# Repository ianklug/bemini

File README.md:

# Bemini
A miniature mechanical keyboard controller with a rotary encoder for staggered-key rhythm games.

Design by [ianklug](https://ianklug.com). Art by [clue](https://clue.graphics).

Special thanks to [Sebastiaan Swinkels](https://github.com/C44Supra) for technical assistance.

Made with [KiCad](https://www.kicad.org/) and [Blender](https://www.blender.org/).

*Please clone this repository using the `--recurse-submodules` flag. Some of the required symbol and footprint libraries will not be included otherwise.*

## Versions

*Please note that the RP2040 models are functional at a hardware level, but software is incomplete.*

The 2.x versions (bemini-rp) use the RP2040 MCU, and require different firmware from the 1.x versions. They also include a few new features and refinements over the 1.x models, including M2 mounting holes and an RGB indicator LED.

The 1.x versions (bemini-atmel) use the Atmega32U4 MCU, in either the MU or AU footprint. These versions are no longer recommended.

## Firmware

Bemini is powered by [QMK Firmware](https://qmk.fm).

Bemini ships with a customized keymap that is ideal for use with many common rhythm games. More information about the default keymap is available [here](https://kayboards.com/pages/bemini-keymap).

You may customize Bemini's keymap by following the instructions in [these documents](https://docs.qmk.fm). This will require a reflash of your board's firmware. Use [QMK Toolbox](https://github.com/qmk/qmk_toolbox) to flash if on Windows or MacOS, or the QMK CLI with avrdude on Linux.

## Printed Parts

The .stl files for Bemini's 3D-printed parts are included in the models directory. I print these parts on a [Prusa i3 MK3S](https://www.prusa3d.com/category/original-prusa-i3-mk3s/) in black PLA on a smooth steel print bed.

The newer turntable (v2) is a single piece, and requires no supports. It should be printed with the top facing down. Infill should be at least 15%. This is the recommended version.

The first turntable (v1) prints in two pieces (main and cap) which snap together. This may improve the quality of some of the touch surfaces if your prints are inconsistent. Print with the flat top of the cap facing down, and the flat ring (the bottom) of the main body facing down. The body will require supports.

The encoder retainer should be printed with the flat part facing down. Slide this piece in between the encoder's legs on the underside of the board to secure the encoder, if you do not wish to solder it in place.

## Manufacturing

**Manufacture at your own risk. I can not guarantee the quality or functionality of boards which are not sold directly by me.**

**Please note that most PCB manufacturers have a minimum order quantity of five units.**

Hand-soldering Beminis from scratch is extremely difficult and NOT recommended due to the small size of the surface-mount components and their pads. Instead, PCB assembly services can source and assemble all the small parts on the bottom of the board. Depending on the manufacturer, you may only need to hand-solder some of the larger parts, such as the USB port and the switch sockets.

I can personally recommend [JLCPCB](https://jlcpcb.com) or [PCBWay](https://pcbway.com/), but most PCB manufacturers should be capable of producing Bemini.

Zipped gerber files are present for the production designs of each variation of Bemini. They are called `<variation>-gerbers-<version>.zip` and should be compatible with most PCB manufacturing services.

If you will be ordering from JLCPCB, use `<variation>-gerbers-jlcpcb-<version>.zip`. These gerbers have the JLCPCB serial number placed in an easily-readable location on the back of the board. Make sure to choose "Specify a location" under "Remove Order Number" so that this number is printed where expected.

Production Beminis are two-layer FR4, 1.6mm thick. The RP2040 versions measure 220x70mm. They are assembled using lead-free solder. BOM and Centroid files are present for each board in the format expected by JLCPCB.

The USB connector is a [GCT USB4085](https://gct.co/connector/usb4085). The hot-swap sockets are [Kailh sockets](https://www.kailhswitch.com/mechanical-keyboard-switches/box-switches/mechanical-keyboard-switches-kailh-pcb-socket.html). The encoder sockets are [Mill-Max 3305 receptacles](https://www.mill-max.com/products/receptacle/3305). The encoder is a [Bourns PES12](https://www.bourns.com/pdfs/pes12.pdf). An [Alps EC12E](https://tech.alpsalpine.com/e/products/category/encorder/sub/02/series/ec12e/) will also work. The RGB LED is a WS2812B.

## License

Shield: [![CC BY-SA 4.0][cc-by-sa-shield]][cc-by-sa]

This work is licensed under a
[Creative Commons Attribution-ShareAlike 4.0 International License][cc-by-sa].

[![CC BY-SA 4.0][cc-by-sa-image]][cc-by-sa]

[cc-by-sa]: http://creativecommons.org/licenses/by-sa/4.0/
[cc-by-sa-image]: https://licensebuttons.net/l/by-sa/4.0/88x31.png
[cc-by-sa-shield]: https://img.shields.io/badge/License-CC%20BY--SA%204.0-lightgrey.svg

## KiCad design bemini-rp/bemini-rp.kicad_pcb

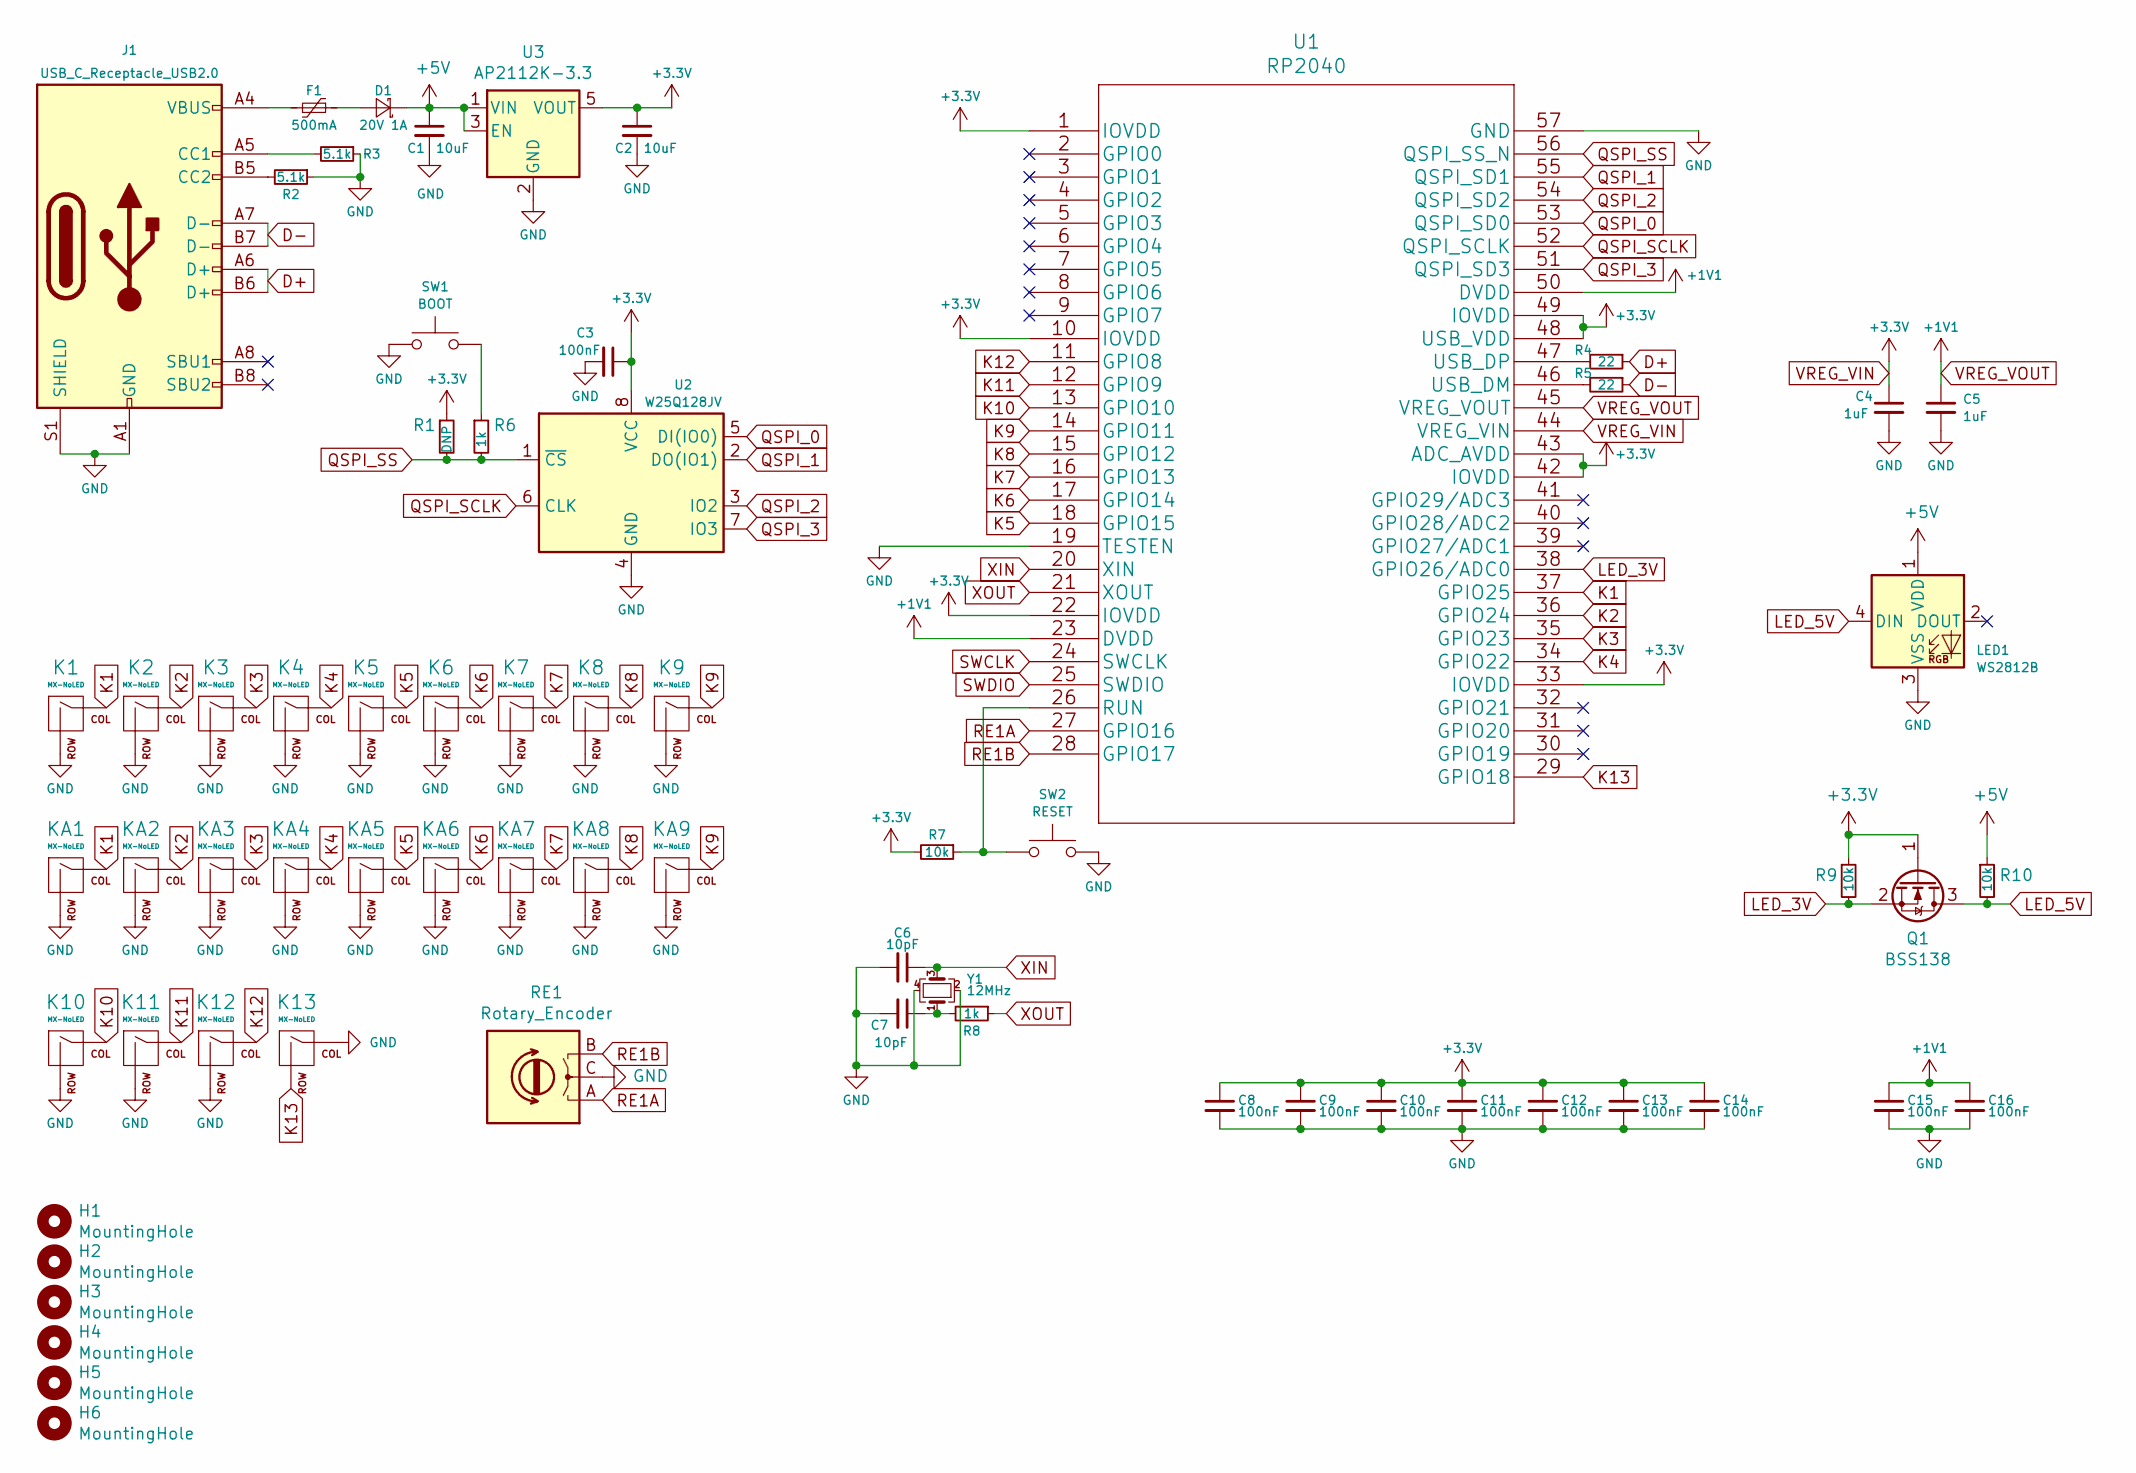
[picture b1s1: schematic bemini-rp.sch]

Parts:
C1, C2: 10uF; C_0402
C3, C8, C9, C10, C11, C12, C13, C14, C15, C16: 100nF; C_0402
C4, C5: 1uF; C_0402
C6, C7: 10pF; C_0402
D1: 20V 1A; D_SOD-323
F1: 500mA; Fuse_0805
H1, H2, H3, H4, H5, H6: MountingHole; MountingHole_2.2mm_M2
J1: USB_C_Receptacle_USB2.0; USB_C_GCT_USB4085
K1, K2, K3, K4, K5, K6, K7, K8, K9, K10, K11, K12, K13: MX-NoLED; Kailh_socket_PG1350
KA1, KA2, KA3, KA4, KA5, KA6, KA7, KA8, KA9: MX-NoLED; Kailh_socket_PG1350
LED1: WS2812B
Q1: BSS138; SOT-23
R1: DNP; R_0402
R2, R3: 5.1k; R_0402
R4, R5: 22; R_0402
R6, R8: 1k; R_0402
R7, R9, R10: 10k; R_0402
RE1: Rotary_Encoder; RotaryEncoder_Alps_EC12E_Vertical_H20mm
SW1: BOOT; TS-1187A-B-A-B
SW2: RESET; TS-1187A-B-A-B
U1: RP2040
U2: W25Q128JV; W25Q128JVPIQ
U3: AP2112K-3.3; SOT-23-5
Y1: 12MHz; Crystal_SMD_3225-4pin_3.2x2.5mm

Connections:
+5V: C1.1, D1.1 (K), LED1.1 (VDD), R10.1, U3.1 (VIN), U3.3 (EN)
D+: J1.A6 (D+), J1.B6 (D+), R4.1
D-: J1.A7 (D-), J1.B7 (D-), R5.1
GND: C1.2, C2.2, C3.2, C4.2, C5.2, C6.2, C7.2, C8.2, C9.2, C10.2, C11.2, C12.2, C13.2, C14.2, C15.2, C16.2, J1.A1 (GND), J1.A12 (GND), J1.B1 (GND), J1.B12 (GND), J1.S1 (SHIELD), K1.2 (ROW), K2.2 (ROW), K3.2 (ROW), K4.2 (ROW), K5.2 (ROW), K6.2 (ROW), K7.2 (ROW), K8.2 (ROW), K9.2 (ROW), K10.2 (ROW), K11.2 (ROW), K12.2 (ROW), K13.1 (COL), KA1.2 (ROW), KA2.2 (ROW), KA3.2 (ROW), KA4.2 (ROW), KA5.2 (ROW), KA6.2 (ROW), KA7.2 (ROW), KA8.2 (ROW), KA9.2 (ROW), LED1.3 (VSS), R2.1, R3.1, RE1.C, SW1.1, SW2.2, U1.19 (TESTEN), U1.57 (GND), U2.4 (GND), U3.2 (GND), Y1.2, Y1.4
K1: K1.1 (COL), KA1.1 (COL), U1.37 (GPIO25)
K2: K2.1 (COL), KA2.1 (COL), U1.36 (GPIO24)
K3: K3.1 (COL), KA3.1 (COL), U1.35 (GPIO23)
K4: K4.1 (COL), KA4.1 (COL), U1.34 (GPIO22)
K5: K5.1 (COL), KA5.1 (COL), U1.18 (GPIO15)
K6: K6.1 (COL), KA6.1 (COL), U1.17 (GPIO14)
K7: K7.1 (COL), KA7.1 (COL), U1.16 (GPIO13)
K8: K8.1 (COL), KA8.1 (COL), U1.15 (GPIO12)
K9: K9.1 (COL), KA9.1 (COL), U1.14 (GPIO11)
K10: K10.1 (COL), U1.13 (GPIO10)
K11: K11.1 (COL), U1.12 (GPIO9)
K12: K12.1 (COL), U1.11 (GPIO8)
K13: K13.2 (ROW), U1.29 (GPIO18)
LED_3V: Q1.2 (S), R9.2, U1.38 (GPIO26/ADC0)
LED_5V: LED1.4 (DIN), Q1.3 (D), R10.2
unnamed: C7.1, R8.2, Y1.1
unnamed: D1.2 (A), F1.1
unnamed: F1.2, J1.A4 (VBUS), J1.A9 (VBUS), J1.B4 (VBUS), J1.B9 (VBUS)
unnamed: J1.A5 (CC1), R3.2
unnamed: J1.B5 (CC2), R2.2
unnamed: R4.2, U1.47 (USB_DP)
unnamed: R5.2, U1.46 (USB_DM)
unnamed: R6.1, SW1.2
unnamed: R7.1, SW2.1, U1.26 (RUN)
QSPI_0: U1.53 (QSPI_SD0), U2.5 (DI(IO0))
QSPI_1: U1.55 (QSPI_SD1), U2.2 (DO(IO1))
QSPI_2: U1.54 (QSPI_SD2), U2.3 (IO2)
QSPI_3: U1.51 (QSPI_SD3), U2.7 (IO3)
QSPI_SCLK: U1.52 (QSPI_SCLK), U2.6 (CLK)
QSPI_SS: R1.2, R6.2, U1.56 (QSPI_SS_N), U2.1 (~CS)
RE1A: RE1.A, U1.27 (GPIO16)
RE1B: RE1.B, U1.28 (GPIO17)
VREG_VIN: C2.1, C3.1, C4.1, C8.1, C9.1, C10.1, C11.1, C12.1, C13.1, C14.1, Q1.1 (G), R1.1, R7.2, R9.1, U1.1 (IOVDD), U1.10 (IOVDD), U1.22 (IOVDD), U1.33 (IOVDD), U1.42 (IOVDD), U1.43 (ADC_AVDD), U1.44 (VREG_VIN), U1.48 (USB_VDD), U1.49 (IOVDD), U2.8 (VCC), U3.5 (VOUT)
VREG_VOUT: C5.1, C15.1, C16.1, U1.23 (DVDD), U1.45 (VREG_VOUT), U1.50 (DVDD)
XIN: C6.1, U1.20 (XIN), Y1.3
XOUT: R8.1, U1.21 (XOUT)

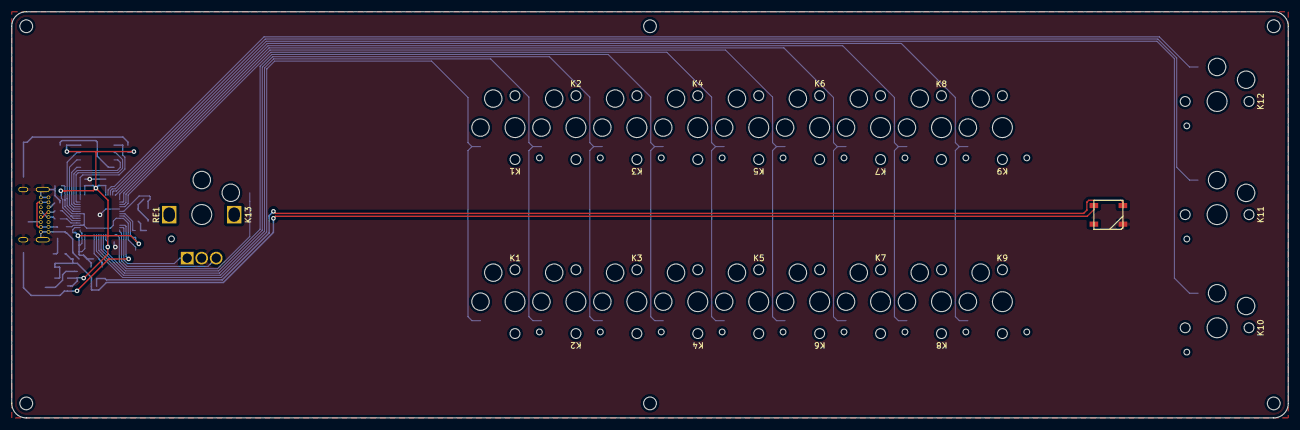
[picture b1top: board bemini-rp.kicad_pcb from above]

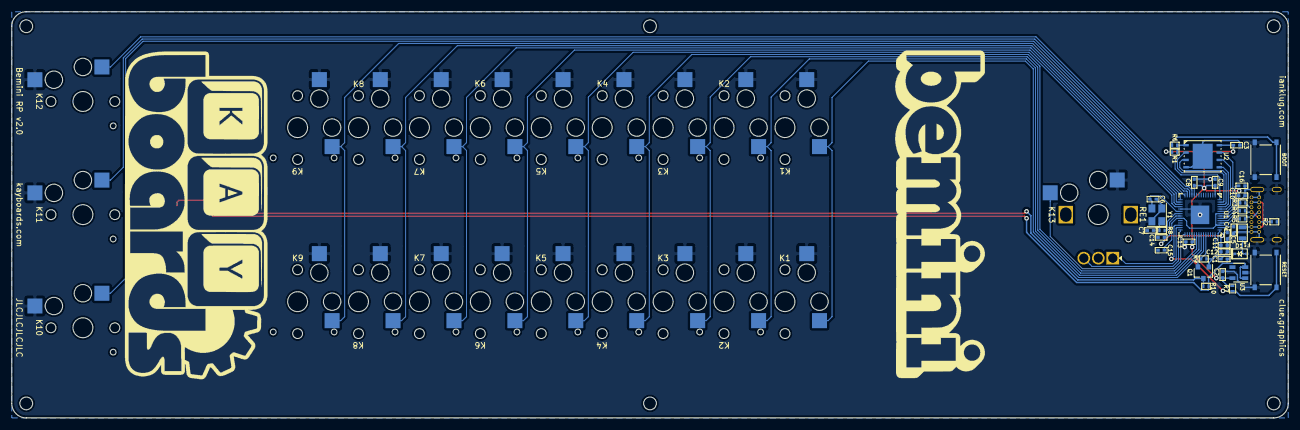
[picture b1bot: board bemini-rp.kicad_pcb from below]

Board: 2 copper layers, 220.0 x 70.0 mm, 66 parts (35 on the bottom side), 40 nets.

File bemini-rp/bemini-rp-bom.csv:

Comment,Designator,Footprint,LCSC Part Number
10uF,"C1, C2",402,C15525
100nF,"C3, C8, C9, C10, C11, C12, C13, C14, C15, C16",402,C1525
1uF,"C4, C5",402,C52923
10pF,"C6, C7",402,C32949
Schottky,D1,SOD-323,C191023
500mA,F1,805,C261942 
BSS138,Q1,SOT-25,C400505
10k,"R7, R9, R10",402,C25744
5.1k,"R2, R3",402,C25905
22,"R4, R5",402,C25092
1k,"R6, R8",402,C25905
TS-1187A-B-A-B,"SW1, SW2",SMD,C318884 
RP2040,U1,QFN-56(7x7),C2040
W25Q128JV,U2,WSON-8_5x6mm,C190862
3.3V,U3,SOT-25,C51118
12MHz,Y1,SMD3225-4P,C255903

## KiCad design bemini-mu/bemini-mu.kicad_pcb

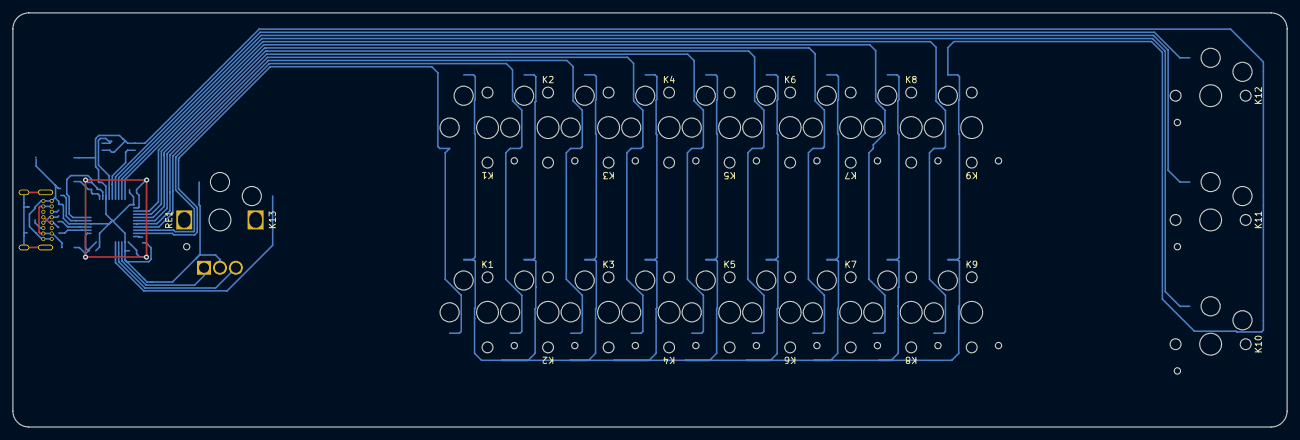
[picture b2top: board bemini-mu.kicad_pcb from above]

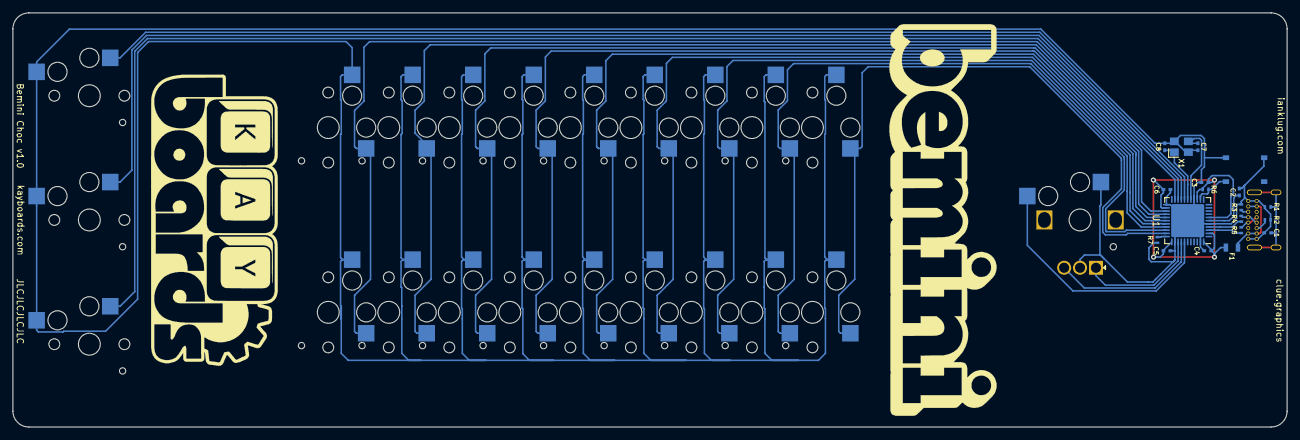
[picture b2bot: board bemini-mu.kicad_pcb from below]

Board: 2 copper layers, 200.0 x 65.0 mm, 43 parts (19 on the bottom side), 30 nets.

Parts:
C1: 4.7nF; C_0402
C2: 1uF; C_0402
C3, C4, C5: 0.1uF; C_0402
C6: 10uF; C_0402
C7, C8: 22pF; C_0402
F1: 500mA; Fuse_0805
J1: USB_C_Receptacle_USB2.0; USB_C_GCT_USB4085
K1, K2, K3, K4, K5, K6, K7, K8, K9, K10, K11, K12, K13: MX-NoLED; Kailh_socket_PG1350
KA1, KA2, KA3, KA4, KA5, KA6, KA7, KA8, KA9: MX-NoLED; Kailh_socket_PG1350
R1: 1M; R_0402
R2, R3: 5.1k; R_0402
R4, R5: 22; R_0402
R6, R7: 10k; R_0402
RE1: Rotary_Encoder; RotaryEncoder_Alps_EC12E_Vertical_H20mm
S1: SW_Push; TS-1187A-B-A-B
U1: ATmega32U4-MU; QFN-44-1EP_7x7mm_P0.5mm_EP5.2x5.2mm
X1: 16MHz; Crystal_SMD_3225-4pin_3.2x2.5mm

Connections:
D+: R4.1, U1.4
D-: R5.1, U1.3
GND: C1.2, C2.2, C3.2, C4.2, C5.2, C6.2, C7.1, C8.1, J1.A1, J1.A12, J1.B1, J1.B12, K1.2, K2.2, K3.2, K4.2, K5.2, K6.2, K7.2, K8.2, K9.2, K10.2, K11.2, K12.2, K13.1, KA1.2, KA2.2, KA3.2, KA4.2, KA5.2, KA6.2, KA7.2, KA8.2, KA9.2, R1.2, R2.1, R3.1, R7.1, RE1.C, S1.1, U1.5, U1.15, U1.23, U1.35, U1.43, U1.45, X1.2, X1.4
K1: K1.1, KA1.1, U1.32
K2: K2.1, KA2.1, U1.31
K3: K3.1, KA3.1, U1.30
K4: K4.1, KA4.1, U1.29
K5: K5.1, KA5.1, U1.28
K6: K6.1, KA6.1, U1.27
K7: K7.1, KA7.1, U1.26
K8: K8.1, KA8.1, U1.25
K9: K9.1, KA9.1, U1.21
K10: K10.1, U1.20
K11: K11.1, U1.19
K12: K12.1, U1.18
K13: K13.2, U1.38
unnamed: C1.1, J1.S1, R1.1
unnamed: C2.1, U1.6
unnamed: C7.2, U1.16, X1.3
unnamed: C8.2, U1.17, X1.1
unnamed: F1.2, J1.A4, J1.A9, J1.B4, J1.B9
unnamed: J1.A5, R3.2
unnamed: J1.A6, J1.B6, R4.2
unnamed: J1.A7, J1.B7, R5.2
unnamed: J1.B5, R2.2
unnamed: R7.2, U1.33
RE1A: RE1.A, U1.36
RE1B: RE1.B, U1.37
RST: R6.2, S1.2, U1.13
VCC: C3.1, C4.1, C5.1, C6.1, F1.1, R6.1, U1.2, U1.7, U1.14, U1.24, U1.34, U1.44

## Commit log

2022-11-05 initial rp2040 commit
2022-11-06 fix dead link
2022-11-17 fix incorrect resistor part number in BOM
2022-11-17 update usb resistors

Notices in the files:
parts and their libraries:
Copyright 2021 Accelerated Designs. All rights reserved.
